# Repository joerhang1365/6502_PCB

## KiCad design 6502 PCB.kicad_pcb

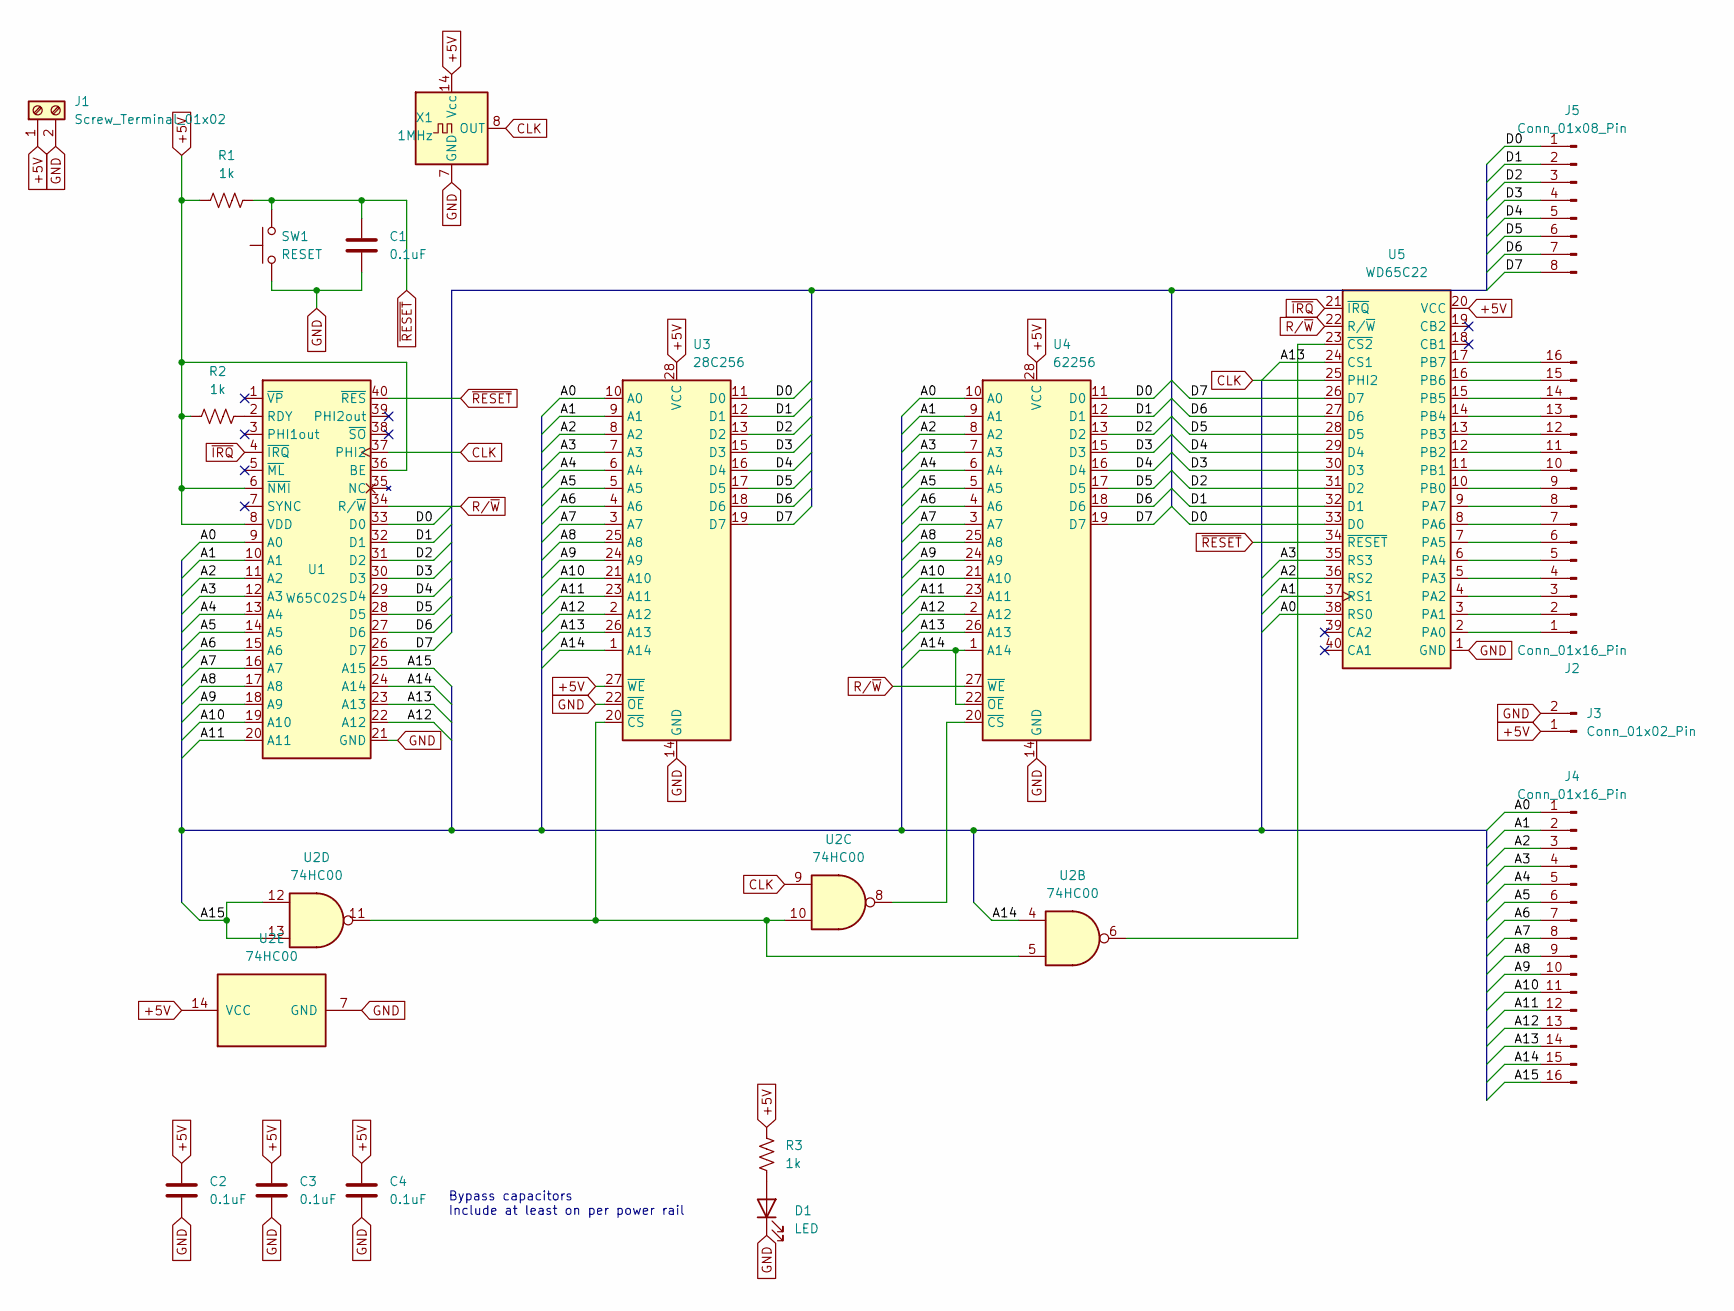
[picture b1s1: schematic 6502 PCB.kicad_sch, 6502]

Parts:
C1, C2, C3, C4: 0.1uF; C_Disc_D6.0mm_W2.5mm_P5.00mm
D1: LED; LED_D5.0mm_Clear
J1: Screw_Terminal_01x02; TerminalBlock_Phoenix_MKDS-1,5-2-5.08_1x02_P5.08mm_Horizont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
J2, J4: Conn_01x16_Pin; PinSocket_1x16_P2.54mm_Vertical
J3: Conn_01x02_Pin; PinSocket_1x02_P2.54mm_Vertical
J5: Conn_01x08_Pin; PinSocket_1x08_P2.54mm_Vertical
R1, R2, R3: 1k; R_Axial_DIN0207_L6.3mm_D2.5mm_P10.16mm_Horizontal
SW1: RESET; SW_PUSH_6mm_H5mm
U1: W65C02S; DIP-40_W15.24mm
U2: 74HC00; DIP-14_W7.62mm
U3: 28C256; DIP-28_W15.24mm
U4: 62256; DIP-28_W15.24mm
U5: WD65C22; DIP-40_W15.24mm
X1: 1MHz; Oscillator_DIP-14

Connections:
+5V: C2.1, C3.1, C4.1, J1.1, J3.1, R1.1, R2.1, R3.2, U1.6 (~NMI), U1.8 (VDD), U1.36 (BE), U2.14 (VCC), U3.27 (~WE), U3.28 (VCC), U4.28 (VCC), U5.20 (VCC), X1.14 (Vcc)
/A0: J4.1, U1.9 (A0), U3.10 (A0), U4.10 (A0), U5.38 (RS0)
/A1: J4.2, U1.10 (A1), U3.9 (A1), U4.9 (A1), U5.37 (RS1)
/A2: J4.3, U1.11 (A2), U3.8 (A2), U4.8 (A2), U5.36 (RS2)
/A3: J4.4, U1.12 (A3), U3.7 (A3), U4.7 (A3), U5.35 (RS3)
/A4: J4.5, U1.13 (A4), U3.6 (A4), U4.6 (A4)
/A5: J4.6, U1.14 (A5), U3.5 (A5), U4.5 (A5)
/A6: J4.7, U1.15 (A6), U3.4 (A6), U4.4 (A6)
/A7: J4.8, U1.16 (A7), U3.3 (A7), U4.3 (A7)
/A8: J4.9, U1.17 (A8), U3.25 (A8), U4.25 (A8)
/A9: J4.10, U1.18 (A9), U3.24 (A9), U4.24 (A9)
/A10: J4.11, U1.19 (A10), U3.21 (A10), U4.21 (A10)
/A11: J4.12, U1.20 (A11), U3.23 (A11), U4.23 (A11)
/A12: J4.13, U1.22 (A12), U3.2 (A12), U4.2 (A12)
/A13: J4.14, U1.23 (A13), U3.26 (A13), U4.26 (A13), U5.24 (CS1)
/A14: J4.15, U1.24 (A14), U2.4, U3.1 (A14), U4.1 (A14), U4.22 (~OE)
/A15: J4.16, U1.25 (A15), U2.12, U2.13
/D0: J5.1, U1.33 (D0), U3.11 (D0), U4.11 (D0), U5.33 (D0)
/D1: J5.2, U1.32 (D1), U3.12 (D1), U4.12 (D1), U5.32 (D1)
/D2: J5.3, U1.31 (D2), U3.13 (D2), U4.13 (D2), U5.31 (D2)
/D3: J5.4, U1.30 (D3), U3.15 (D3), U4.15 (D3), U5.30 (D3)
/D4: J5.5, U1.29 (D4), U3.16 (D4), U4.16 (D4), U5.29 (D4)
/D5: J5.6, U1.28 (D5), U3.17 (D5), U4.17 (D5), U5.28 (D5)
/D6: J5.7, U1.27 (D6), U3.18 (D6), U4.18 (D6), U5.27 (D6)
/D7: J5.8, U1.26 (D7), U3.19 (D7), U4.19 (D7), U5.26 (D7)
CLK: U1.37 (PHI2), U2.9, U5.25 (PHI2), X1.8 (OUT)
GND: C1.2, C2.2, C3.2, C4.2, D1.1 (K), J1.2, J3.2, SW1.1, U1.21 (GND), U2.7 (GND), U3.14 (GND), U3.22 (~OE), U4.14 (GND), U5.1 (GND), X1.7 (GND)
unnamed: D1.2 (A), R3.1
unnamed: J2.1, U5.2 (PA0)
unnamed: J2.2, U5.3 (PA1)
unnamed: J2.3, U5.4 (PA2)
unnamed: J2.4, U5.5 (PA3)
unnamed: J2.5, U5.6 (PA4)
unnamed: J2.6, U5.7 (PA5)
unnamed: J2.7, U5.8 (PA6)
unnamed: J2.8, U5.9 (PA7)
unnamed: J2.9, U5.10 (PB0)
unnamed: J2.10, U5.11 (PB1)
unnamed: J2.11, U5.12 (PB2)
unnamed: J2.12, U5.13 (PB3)
unnamed: J2.13, U5.14 (PB4)
unnamed: J2.14, U5.15 (PB5)
unnamed: J2.15, U5.16 (PB6)
unnamed: J2.16, U5.17 (PB7)
unnamed: R2.2, U1.2 (RDY)
unnamed: U2.5, U2.10, U2.11, U3.20 (~CS)
unnamed: U2.8, U4.20 (~CS)
unnamed: U2.6, U5.23 (~CS2)
R/~W: U1.34 (R/~W), U4.27 (~WE), U5.22 (R/~W)
~IRQ: U1.4 (~IRQ), U5.21 (~IRQ)
~RESET: C1.1, R1.2, SW1.2, U1.40 (~RES), U5.34 (~RESET)

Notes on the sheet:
Bypass capacitors Include at least on per power rail

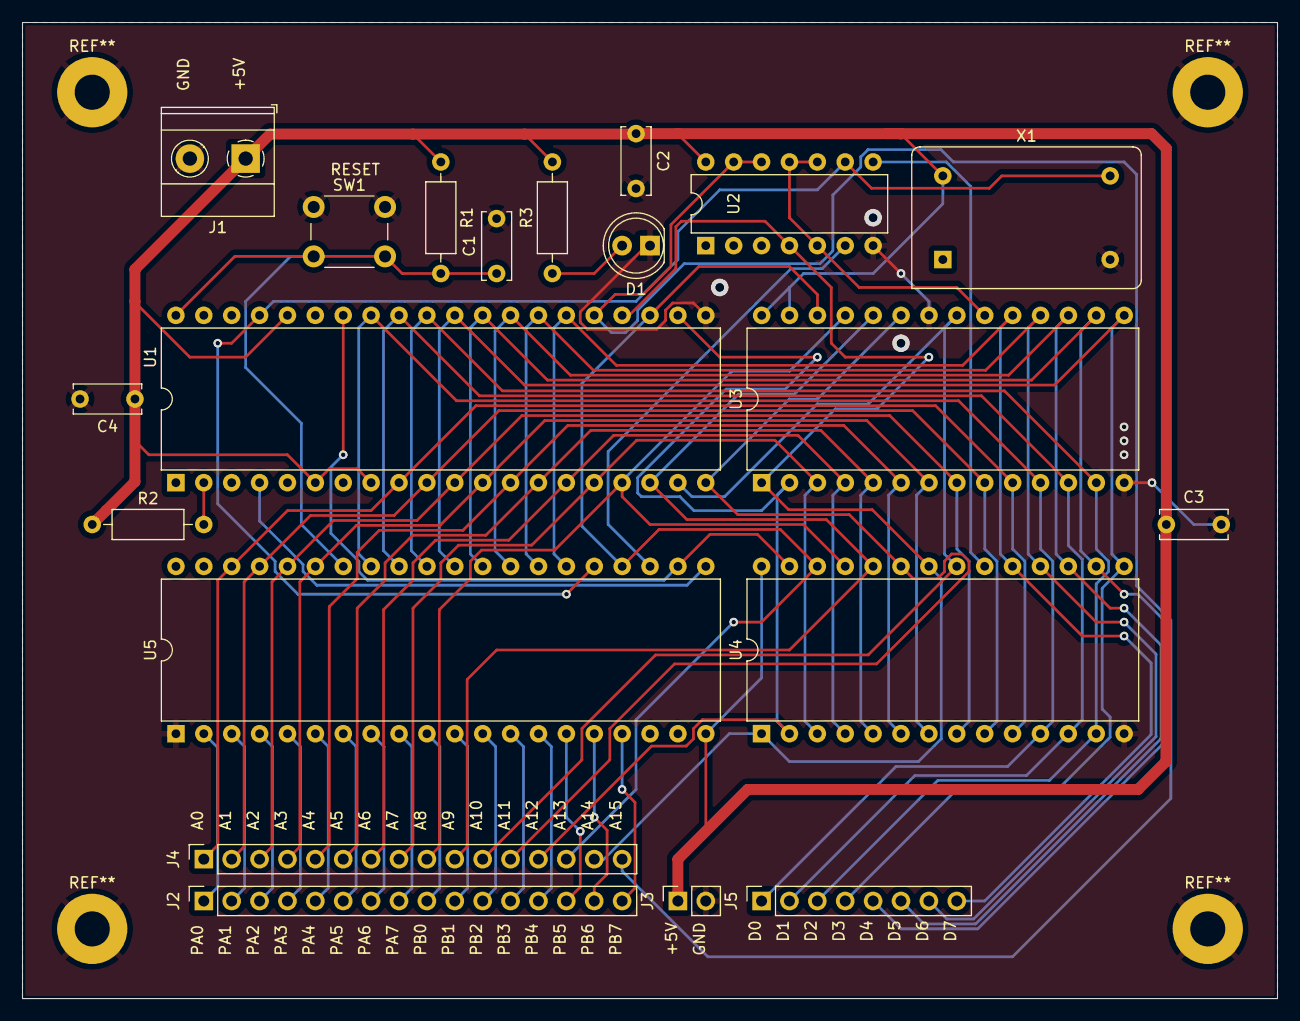
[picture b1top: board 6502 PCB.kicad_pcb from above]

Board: 2 copper layers, 114.3 x 88.9 mm, 20 parts (0 on the bottom side), 51 nets.

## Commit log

2023-09-08 think i finished schematic
2023-09-08 bumb
2023-09-12 aaaaaaaaaaaaaaaaaaaa
2023-09-18 Add files via upload
    almost done with pcb design
2023-09-20 Add files via upload
    redid pretty much everything
2023-09-22 lets gooso
2023-09-23 pretty much done
2023-10-16 pls work
2023-10-16 maybe wrok
2024-01-17 removed extra stuff
2024-05-17 changed schematic
2024-05-19 aaaa
2024-09-15 changed schematic a bunch
2024-09-15 finished PCB Design
2024-09-16 aaaaaaaaaaaaaaahhhhhhhhhhhhhhhhhhhhhhh
